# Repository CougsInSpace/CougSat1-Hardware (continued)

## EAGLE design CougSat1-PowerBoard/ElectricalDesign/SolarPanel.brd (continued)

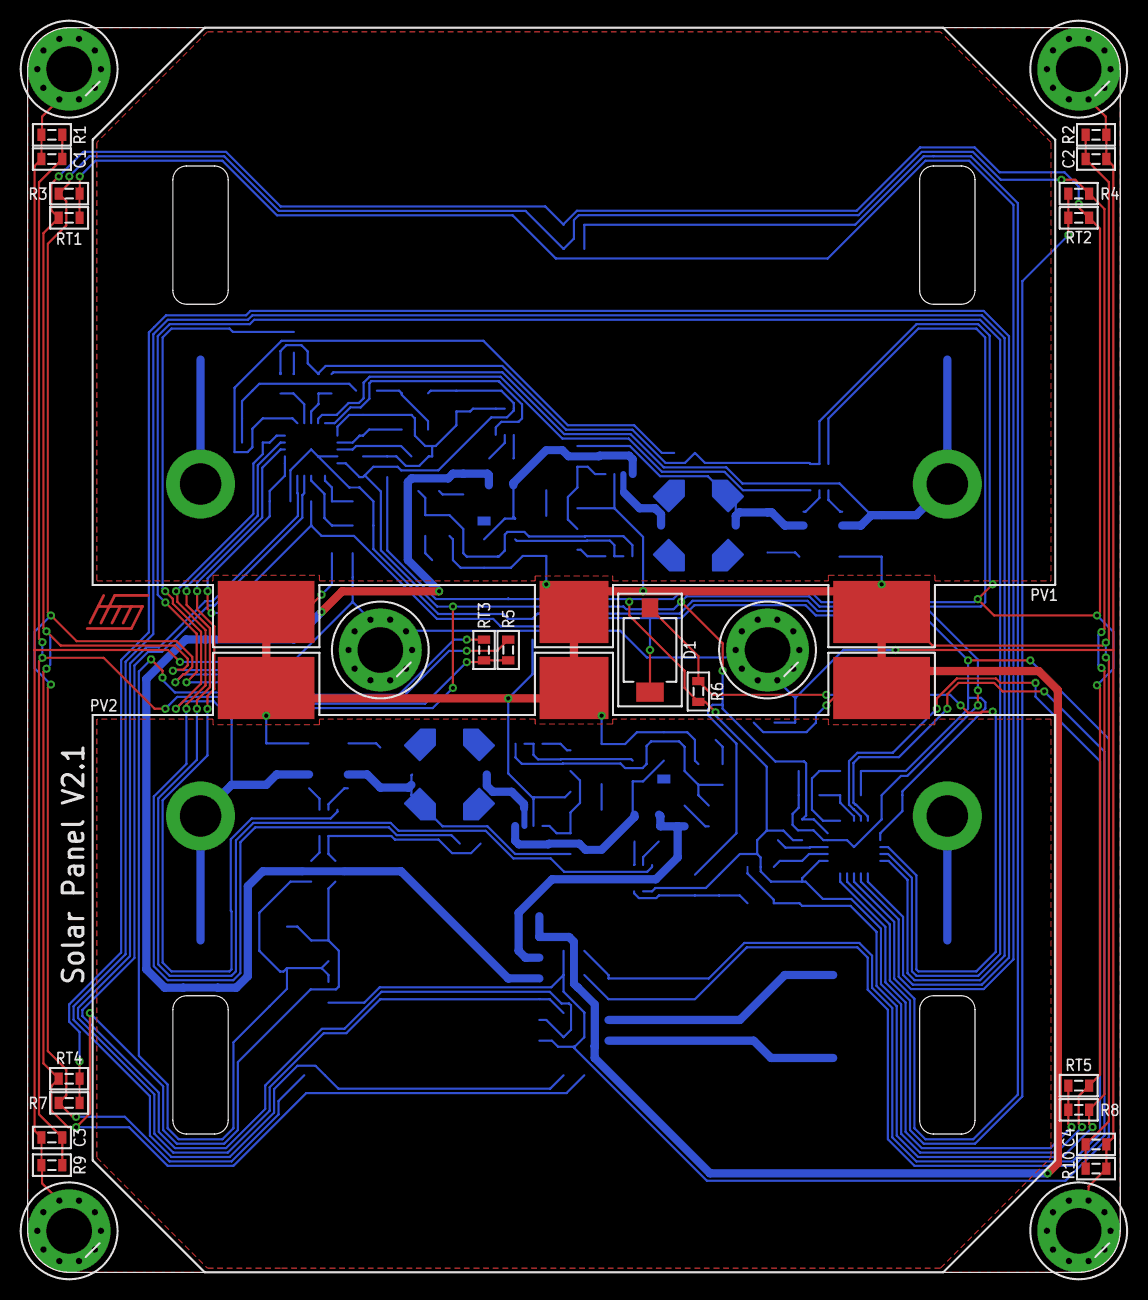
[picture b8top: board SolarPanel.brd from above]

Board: 2 copper layers, 79.0 x 90.0 mm, 129 parts (100 on the bottom side), 74 nets.

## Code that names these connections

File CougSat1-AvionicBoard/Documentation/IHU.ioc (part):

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Mcu.Name=STM32L496V(E-G)Tx
Mcu.Package=LQFP100
Mcu.UserName=STM32L496VGTx
PA0.Signal=ADCx_IN5
PA1.Signal=ADCx_IN6
PA10.Mode=Synchronous
PA10.Signal=USART1_RX
PA11.Mode=Host_Only
PA11.Signal=USB_OTG_FS_DM
PA12.Mode=Host_Only
PA12.Signal=USB_OTG_FS_DP
PA13\ (JTMS/SWDIO).Mode=JTAG_4_pins
PA13\ (JTMS/SWDIO).Signal=SYS_JTMS-SWDIO
PA14\ (JTCK/SWCLK).Mode=JTAG_4_pins
PA14\ (JTCK/SWCLK).Signal=SYS_JTCK-SWCLK
PA15\ (JTDI).Mode=JTAG_4_pins
PA15\ (JTDI).Signal=SYS_JTDI
PA2.Signal=ADCx_IN7
PA3.Signal=ADCx_IN8
PA4.Signal=ADCx_IN9
PA5.Mode=Full_Duplex_Master
PA5.Signal=SPI1_SCK
PA6.Mode=Full_Duplex_Master
PA6.Signal=SPI1_MISO
PA7.Mode=Full_Duplex_Master
PA7.Signal=SPI1_MOSI
PA8.Mode=Synchronous
PA8.Signal=USART1_CK
PA9.Mode=Synchronous
PA9.Signal=USART1_TX
PB0.Signal=ADCx_IN15
PB1.Signal=ADCx_IN16
PB10.Mode=Synchronous
PB10.Signal=USART3_TX
PB11.Mode=Synchronous
PB11.Signal=USART3_RX
PB12.Mode=Synchronous
PB12.Signal=USART3_CK
PB13.Mode=I2C
PB13.Signal=I2C2_SCL
PB14.Mode=I2C
PB14.Signal=I2C2_SDA
PB3\ (JTDO/TRACESWO).Mode=JTAG_4_pins
PB3\ (JTDO/TRACESWO).Signal=SYS_JTDO-SWO
PB6.Mode=I2C
PB6.Signal=I2C1_SCL
PB7.Mode=I2C
PB7.Signal=I2C1_SDA
PC0.Signal=ADCx_IN1
PC1.Signal=ADCx_IN2
PC10.Mode=SD_4_bits_Wide_bus
PC10.Signal=SDMMC1_D2
PC11.Mode=SD_4_bits_Wide_bus
PC11.Signal=SDMMC1_D3
PC12.Mode=SD_4_bits_Wide_bus
PC12.Signal=SDMMC1_CK
PC14-OSC32_IN\ (PC14).Mode=LSE-External-Oscillator
PC14-OSC32_IN\ (PC14).Signal=RCC_OSC32_IN
PC15-OSC32_OUT\ (PC15).Mode=LSE-External-Oscillator
PC15-OSC32_OUT\ (PC15).Signal=RCC_OSC32_OUT
PC4.Signal=ADCx_IN13
PC5.Signal=ADCx_IN14
PC8.Mode=SD_4_bits_Wide_bus
PC8.Signal=SDMMC1_D0
PC9.Mode=SD_4_bits_Wide_bus
PC9.Signal=SDMMC1_D1
PD2.Mode=SD_4_bits_Wide_bus
PD2.Signal=SDMMC1_CMD
PD5.Mode=Asynchronous
PD5.Signal=USART2_TX
PD6.Mode=Asynchronous
PD6.Signal=USART2_RX
PH0-OSC_IN\ (PH0).Mode=HSE-External-Oscillator
PH0-OSC_IN\ (PH0).Signal=RCC_OSC_IN
PH1-OSC_OUT\ (PH1).Mode=HSE-External-Oscillator
PH1-OSC_OUT\ (PH1).Signal=RCC_OSC_OUT
RCC.HSE_VALUE=16000000
RCC.SYSCLKFreq_VALUE=80000000
RCC.SYSCLKSource=RCC_SYSCLKSOURCE_PLLCLK

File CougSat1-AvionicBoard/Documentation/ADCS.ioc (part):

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Mcu.Name=STM32L476R(C-E-G)Tx
Mcu.Package=LQFP64
Mcu.UserName=STM32L476RGTx
PA1.Signal=S_TIM5_CH2
PA10.Mode=Asynchronous
PA10.Signal=USART1_RX
PA13\ (JTMS-SWDIO).Mode=JTAG_4_pins
PA13\ (JTMS-SWDIO).Signal=SYS_JTMS-SWDIO
PA14\ (JTCK-SWCLK).Mode=JTAG_4_pins
PA14\ (JTCK-SWCLK).Signal=SYS_JTCK-SWCLK
PA15\ (JTDI).Mode=JTAG_4_pins
PA15\ (JTDI).Signal=SYS_JTDI
PA2.Signal=S_TIM5_CH3
PA5.Mode=Full_Duplex_Master
PA5.Signal=SPI1_SCK
PA6.Mode=Full_Duplex_Master
PA6.Signal=SPI1_MISO
PA7.Mode=Full_Duplex_Master
PA7.Signal=SPI1_MOSI
PA9.Mode=Asynchronous
PA9.Signal=USART1_TX
PB10.Mode=I2C
PB10.Signal=I2C2_SCL
PB11.Mode=I2C
PB11.Signal=I2C2_SDA
PB3\ (JTDO-TRACESWO).Mode=JTAG_4_pins
PB3\ (JTDO-TRACESWO).Signal=SYS_JTDO-SWO
PB6.Signal=S_TIM4_CH1
PB7.Signal=S_TIM4_CH2
PB8.Signal=S_TIM4_CH3
PB9.Signal=S_TIM4_CH4
PC0.Mode=I2C
PC0.Signal=I2C3_SCL
PC1.Mode=I2C
PC1.Signal=I2C3_SDA
PC14-OSC32_IN\ (PC14).Mode=LSE-External-Oscillator
PC14-OSC32_IN\ (PC14).Signal=RCC_OSC32_IN
PC15-OSC32_OUT\ (PC15).Mode=LSE-External-Oscillator
PC15-OSC32_OUT\ (PC15).Signal=RCC_OSC32_OUT
RCC.HSE_VALUE=8000000

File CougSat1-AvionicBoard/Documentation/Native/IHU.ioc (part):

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Mcu.Name=STM32L476R(C-E-G)Tx
Mcu.Package=LQFP64
Mcu.UserName=STM32L476RGTx
PA13\ (JTMS-SWDIO).Mode=JTAG_4_pins
PA13\ (JTMS-SWDIO).Signal=SYS_JTMS-SWDIO
PA14\ (JTCK-SWCLK).Mode=JTAG_4_pins
PA14\ (JTCK-SWCLK).Signal=SYS_JTCK-SWCLK
PA15\ (JTDI).Mode=JTAG_4_pins
PA15\ (JTDI).Signal=SYS_JTDI
PA5.Mode=Full_Duplex_Master
PA5.Signal=SPI1_SCK
PA6.Mode=Full_Duplex_Master
PA6.Signal=SPI1_MISO
PA7.Mode=Full_Duplex_Master
PA7.Signal=SPI1_MOSI
PB10.Mode=Full_Duplex_Master
PB10.Signal=SPI2_SCK
PB11.Mode=I2C
PB11.Signal=I2C2_SDA
PB13.Mode=I2C
PB13.Signal=I2C2_SCL
PB3\ (JTDO-TRACESWO).Mode=JTAG_4_pins
PB3\ (JTDO-TRACESWO).Signal=SYS_JTDO-SWO
PB6.Mode=I2C
PB6.Signal=I2C1_SCL
PB7.Mode=I2C
PB7.Signal=I2C1_SDA
PC10.Mode=Full_Duplex_Master
PC10.Signal=SPI3_SCK
PC11.Mode=Full_Duplex_Master
PC11.Signal=SPI3_MISO
PC12.Mode=Full_Duplex_Master
PC12.Signal=SPI3_MOSI
PC2.Mode=Full_Duplex_Master
PC2.Signal=SPI2_MISO
PC3.Mode=Full_Duplex_Master
PC3.Signal=SPI2_MOSI
RCC.HSE_VALUE=8000000
board=custom

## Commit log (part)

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2019-07-08 Updated battery protection and current monitoring
2019-07-08 Updated separation switching
2019-07-08 Resolved Errors
2019-07-09 Revision 1.1
    Made changes to fix errors listed for design document and schematic
2019-07-09 Changed output switching to ideal diodes
2019-07-10 Updated Off-sheet Connectors
2019-07-10 Updated ADC Address
2019-07-10 Fixed Off-Sheet Connector
2019-07-12 Added ADCs
2019-07-12 Fixed ERC errors
2019-07-12 Umbilical Fix
2019-07-13 Fixed formatting
2019-07-17 Minor schematic asthetic changes
2019-07-17 Weed lamp -> Grow lamp
2019-07-17 Finished Schematic and Updated ADCS Design Doc
2019-07-17 Executed Comms test 3.2
2019-07-18 Updated ADCS Design Doc
2019-07-18 Added IFJR and IHU Design Docs
2019-07-18 Executed Comms Test 3.10, 3.8
2019-07-24 Merged and fixed conflicts
2019-07-26 Placed holes
2019-07-26 Performed all backplane tests
2019-07-26 Fixed typo
2019-07-26 Executed Test 3.10-9V, 3.13, & 3.14
2019-07-27 Changed version number and exported to PDF
2019-07-27 Updated design document
2019-07-28 Fixed mCAD merge
2019-07-28 Fixed Parts Placement
2019-07-28 Created Shapes
2019-07-29 Drew tKeepout for deployables
2019-07-30 Moved Parts Out of Restricted Area
2019-07-31 Update -ZPanel.sch
    Ready for re-review
2019-07-31 Tested LDOs and I2C bus
2019-07-31 Updated Umbilical
2019-08-01 Moved decoupling capacitors
2019-08-01 Fixed typos
2019-08-03 Routed Initial Traces
2019-08-04 Began EPS part placement
2019-08-05 Revised Schematic and Began Board Placement
2019-08-05 Exported Schematic to PDF
2019-08-10 Placed most parts
    Fixes #483
2019-08-11 Fixed solar panel
2019-08-12 Updated Umbilical Doc
2019-08-13 Revised Schematic
2019-08-13 Revised IFJR Design Doc
2019-08-16 Changed EPS to 4 layer
2019-08-18 Added cameras
2019-08-18 Routed I2C
2019-08-19 Laid out output and battery protection blocks
2019-08-21 Laid out 3.3V-A
2019-08-23 Laid out PV input 0 & 1 and moved 3V3-B regulator
2019-08-25 Updated Block Diagram
2019-08-27 Laid out 3.3V-B and B side PV inputs
2019-08-29 Laid out VIN and battery current sense
2019-08-30 Added geiger counter
2019-08-31 Laid out battery B
2019-09-08 Created design document
2019-09-08 Added GPIO Expander
2019-09-08 Rerouted Traces
2019-09-08 Updated RF
2019-09-09 added Mac files to gitignore
2019-09-09 Laid out JTAG, BH-0, and remaining ADC
2019-09-10 Laid out remaining signals
2019-09-11 Final asthetic changes, exported pdf
2019-09-13 1.0.3
    Ready for review
2019-09-14 Adjusted trace layout and polygons
2019-09-14 Placed reference designators
2019-09-15 Added test cases
2019-09-15 Added structure to design document
2019-09-15 Document block diagram section
2019-09-16 Fixed formatting and removed bad files
2019-09-18 Changed AVDD to AVDD-0
2019-09-18 Updated Test Cases
2019-09-18 Exported to PDF
2019-09-19 Design Doc
2019-09-20 Updated tests and off-sheet connectors
2019-09-22 Added dcaps, wrote more documentation
2019-09-22 Exported PDF Added Balancing
2019-09-22 Generated Gerber File
2019-09-22 Added Revision Number
2019-09-22 Design Doc ready for review
    Layout is extremely rough
2019-09-22 Finished schematic section documentation
2019-09-22 Removed bad files
2019-09-23 Removed gitignored files
2019-09-24 Exported pdfs and gerbers
2019-09-24 Added GPIO descriptions
2019-09-25 Added Three M2 Holes
2019-09-25 Fixed Mounting Holes And Pico Lock
2019-09-25 Changed Board Size
2019-09-26 Wrote geiger counter functional tests
2019-09-26 Added board thickness to document
2019-09-26 Fixed The Last Issues
2019-09-26 Fixed DRC issues
2019-09-26 FIxed Revision Number
2019-09-27 Removed pull up from current sense
2019-09-29 Addressed feedback in schematic section
2019-09-29 Added buffers on I2C and SPI busses
2019-09-29 Fixed RF Traces
2019-09-30 Exported PDFs
2019-10-02 Minor schematic changes
2019-10-04 Switched out old ADCs for new ADCs
2019-10-06 Switched a DGND to AGND
2019-10-06 Laid out RF
2019-10-06 Finished items listed
    Comments:
    -Gabe verified AS1 low AS0 high
    -Unsure about section 3 formatting
2019-10-06 Ready for re-review
    Fixed issues mentioned before.
2019-10-06 Placed Large Components
2019-10-07 Added dcaps to buffers, specified 7b I2C addresses
2019-10-07 Fixed formatting and adjusted antenna tests
2019-10-08 Changed photodiode circuit
2019-10-09 Stuffed addresses on variants, exported PDFs
2019-10-09 Modified Photodiode
2019-10-10 Updated Photodiode Schematic
2019-10-10 Placed components
2019-10-11 Routed everything
2019-10-12 Moved photodiode into shield, placed analog components
2019-10-14 Tested uplink and downlink chains
2019-10-14 Laid out analog traces
2019-10-16 Optimized Traces
2019-10-17 Added Decoupling Capacitor
2019-10-20 Updated Document
2019-10-20 Exported Files
2019-10-21 Addressed feedback
2019-10-21 Generated gerbers
2019-10-23 Fixed chematic off-sheet connectors
2019-10-23 Fixed final DRC errors and re-exported gerbers
2019-10-23 Implemented MOD 7, 9 and updated libraries
2019-10-23 Reallocated microcontroller pins and added baseband filters to LTSpice
2019-10-24 Fixed Errors
2019-10-27 Updated microcontroller, ADCs, RF clock generators, and power rails
2019-10-27 Updated buffer connections
    Connected SPI and I2C to buffers
2019-10-27 Revert "Updated buffer connections"
    This reverts commit 97c00d36a388c3aa67f6eef2402791ba84bf0edd.
2019-10-28 Addressed most feedback points
2019-10-28 Addressed document feedback
2019-10-28 Completed Schematic
    Fixes #185
    Added powerlines to buffers
    Labeled aesthetics in&out to appropriate data lines.
2019-10-29 Finished Placing Components, Began Wiring
2019-10-29 Deleted Empty Sheets
2019-10-30 Replaced DAC with 27-0006
2019-10-30 Updated 700mm PA
2019-10-31 Added Variant Label
2019-11-03 Updated 230mm PA and removed 9V and -3.3V supplies
2019-11-03 Placed AVDD Circuits and Ground Straps
2019-11-04 Added RF Trace Constraints
2019-11-04 Tested 3.1, 3.2, 3.12, 3.13, 3.14, 3.15, 3.16
2019-11-04 Updated Comms schematic design section
2019-11-04 Updated layout constraints and tests
2019-11-07 Updated photodiode circuit
2019-11-07 Exported Schematic
2019-11-07 Created mCAD and updated board reference designators and RF soldermask
2019-11-07 Wrote RF test cases
2019-11-08 Began part placement
2019-11-09 Placed Comms parts
2019-11-09 Laid out decapaps for the RF chips
2019-11-09 Changed isolated ground to a solid DGND and relaying on layout to ensure good layout
2019-11-10 Laid out 230mm radio
2019-11-10 Laid out 700mm modulator
2019-11-10 Addressed feedback, exported PDFs
2019-11-10 Minor Change
2019-11-10 Correct File
2019-11-11 Tested Most Resistances
2019-11-13 Layout 1.0.0
2019-11-14 Revert "Layout 1.0.0"
    This reverts commit 992a898be94d747baefa5f2d3c94eef64dce9a72.
2019-11-14 Revert "Layout 1.0.0"
    This reverts commit 45e26b36c6b6eae2ae3e254edbdc3df9bd2e5650.
2019-11-14 Layout 1.0.1
    Layout is ready for review. I changed the order of thermal inputs to the ADC for layout purposes on the schematic side also
2019-11-14 Layout for -Z 1.0.1
2019-11-15 Laid out SPI bus, regulator, and JTAG
2019-11-15 Layout 1.0.2
    Ready for RF
2019-11-17 Laid out ADCs and 700mm thermistors and SPI
2019-11-17 Tested 3.3V regulator
2019-11-19 Laid out remaining traces
2019-11-19 Adjusted silkscreen
2019-11-19 Performed before pwoer on check
2019-11-19 Fixed photodiode circuit
2019-11-19 Addressed all feedback
2019-11-20 Fixed test notes
2019-11-21 Touch-ups
2019-11-21 Created mCAD, fixed silkscreen
2019-11-28 Adjusted ground pour and R84 ref des
2019-12-08 executed test 3.1
2020-01-15 outline for the interposer documentation
    corrected file
2020-01-19 Routed Most Traces
2020-01-20 Removed 23cm from link budget
2020-01-20 Removed 230mm circuits
2020-01-23 Ready for review
    Ripped up RF traces
2020-01-26 Photodiode Test
2020-01-27 Placed most components for battery chargers
2020-01-28 Placed most remaining components
2020-01-30 Updated Layout Z
    Updated minimizing VREF and adding R1 to connect DGND to PGND
2020-01-30 Update Layout -Z
    Ignore last one this one gud
2020-01-30 Laid out solar panel
2020-01-30 Really laid it out
2020-01-30 Updated -Z Layout
    Last one bad this 1 gud
2020-01-31 Tested antenna
2020-02-01 Added Germination Payload Temperature ADC to C&DH-Design
2020-02-01 Added Camera I2C Addresses to C&DH-Design
2020-02-02 Tested regulator
2020-02-02 Tested Antenna frequency
2020-02-07 Update -ZPanel.brd
    - Fixed layout concerning decoupling caps and other space inconsistencies
2020-02-07 GPS test
2020-02-07 Revert "Board File Became Corrupted"
    This reverts commit 1ea1317df9c400dd9955655996187b1771273903.
2020-02-07 Board, error
    Board almost ready, error during save&push
2020-02-08 Fixed merge conflicts
2020-02-09 Made changes
    requested by HMS Hendrik
2020-02-10 Laid out battery chargers and ADCs
2020-02-10 Finished laying out traces
2020-02-10 Fixed corrupt files
2020-02-10 Turned doc into pdf
2020-02-10 Made changes
    As requested by Hendrik
2020-02-11 Revert "Turned doc into pdf"
    This reverts commit 38009d4cd5db41ee536914e11902b1950be8afb5.
2020-02-11 Removed Unused Connectors, Shrunk Outline
2020-02-12 Update -ZPanel.brd
    Added cross hatching and moved the reference designators into visible spots. Also fixed some space inconsistencies again.
2020-02-12 Made board and schematic pretty again
2020-02-12 Recovered Board FIle
2020-02-13 Update -ZPanel.brd
    Fixed weirdness
2020-02-13 Finished Routing C&DH ADC
2020-02-13 Adjusted silkscreen and exported gerbers
2020-02-13 Created mCAD
2020-02-14 Fixed minor routing asthetic issue
2020-02-16 Updated mCAD decal
2020-02-17 Fixed PDFs
2020-02-17 Schematic Completed
2020-02-19 Routed Some Power
2020-02-21 Implement schematic changes
2020-02-23 made appropriate changes
2020-02-23 Changed resistors
2020-02-23 Revised changes mentioned in PR
2020-02-23 Placed critical location components
2020-02-25 Completed Germination Payload System Doc 1.0
2020-02-26 Removed unhelpful copper
2020-02-26 Update 2/26/2020
2020-02-28 Update 2/27/2020
    Added Signature
2020-02-28 Fixed EPS interferences
2020-02-28 Fixed mCAD interferences
2020-02-28 Added interposer PCB
2020-03-01 Changed resistor in documentation
2020-03-01 Began Routing DGND
2020-03-01 Imported updated solar panel heatsink
2020-03-02 Laid out output switching
2020-03-05 Made mCAD and updated board
2020-03-08 Germ Payload System Design Doc Update
2020-03-08 fixed changes to document
2020-03-08 fixed doc issues
2020-03-08 schematic updated
2020-03-08 Battery tested and meauserd
2020-03-08 Asthetic changes
2020-03-09 made more changes required
2020-03-09 Wrote most other tests
2020-03-10 Added battery schematic
2020-03-10 Renamed word files
2020-03-11 Began output current sensing layout
2020-03-21 Worked on layout
2020-10-06 Laid out µController
2020-10-06 Imported structure changes
2020-10-20 Updated germination chamber
2020-10-22 Updated structure for wire harness, updated wire harness
2020-12-04 Fixed silkscreen and off-sheet connectors
2020-12-05 Exported gerbers and updated mCAD
2020-12-05 Updated Linguist settings
2021-02-02 Regenerated gerbers v1.2.1 with updated card library part
2021-03-04 Edited I²C design constraints
2021-09-05 Did some testing
2021-09-05 Executed test 3.5
2021-10-10 Routed 4 Layer Avionics Board
2021-10-15 Adjusted silkscreen and poured polygons
2021-10-26 Added signature
2021-10-27 Produced mCAD
2021-10-31 Added antenna receive test descriptions.
    The descriptions for antenna receive tests 1 and 2 were added to the ground station documentation.
2021-12-05 Updated testing
2022-02-25 Testing and Data
2022-04-20 Added Orion B16 into schematic
2022-09-04 update battery testing
2022-09-04 panel testing
2022-09-11 1.4.0 orion added
2022-09-11 Revert "1.4.0 orion added"
    This reverts commit 7dfbb0be5b35fa42da53217a2521a1aa9a7b883b.
2022-09-18 Added Orion B16
2022-09-18 added Orion in brd layout
2022-10-30 short testing
2022-11-03 completed short testing
2022-12-30 Revert "Electrically isolated U27"
    This reverts commit fd3c505bcf3a17452fe7ea63f5a24548112525a7.
2022-12-31 added heatsink traces
2022-12-31 Adjusted layout
2023-01-12 Added nFET
2023-01-15 added new gerbers
2023-02-26 short testing
    everything works
